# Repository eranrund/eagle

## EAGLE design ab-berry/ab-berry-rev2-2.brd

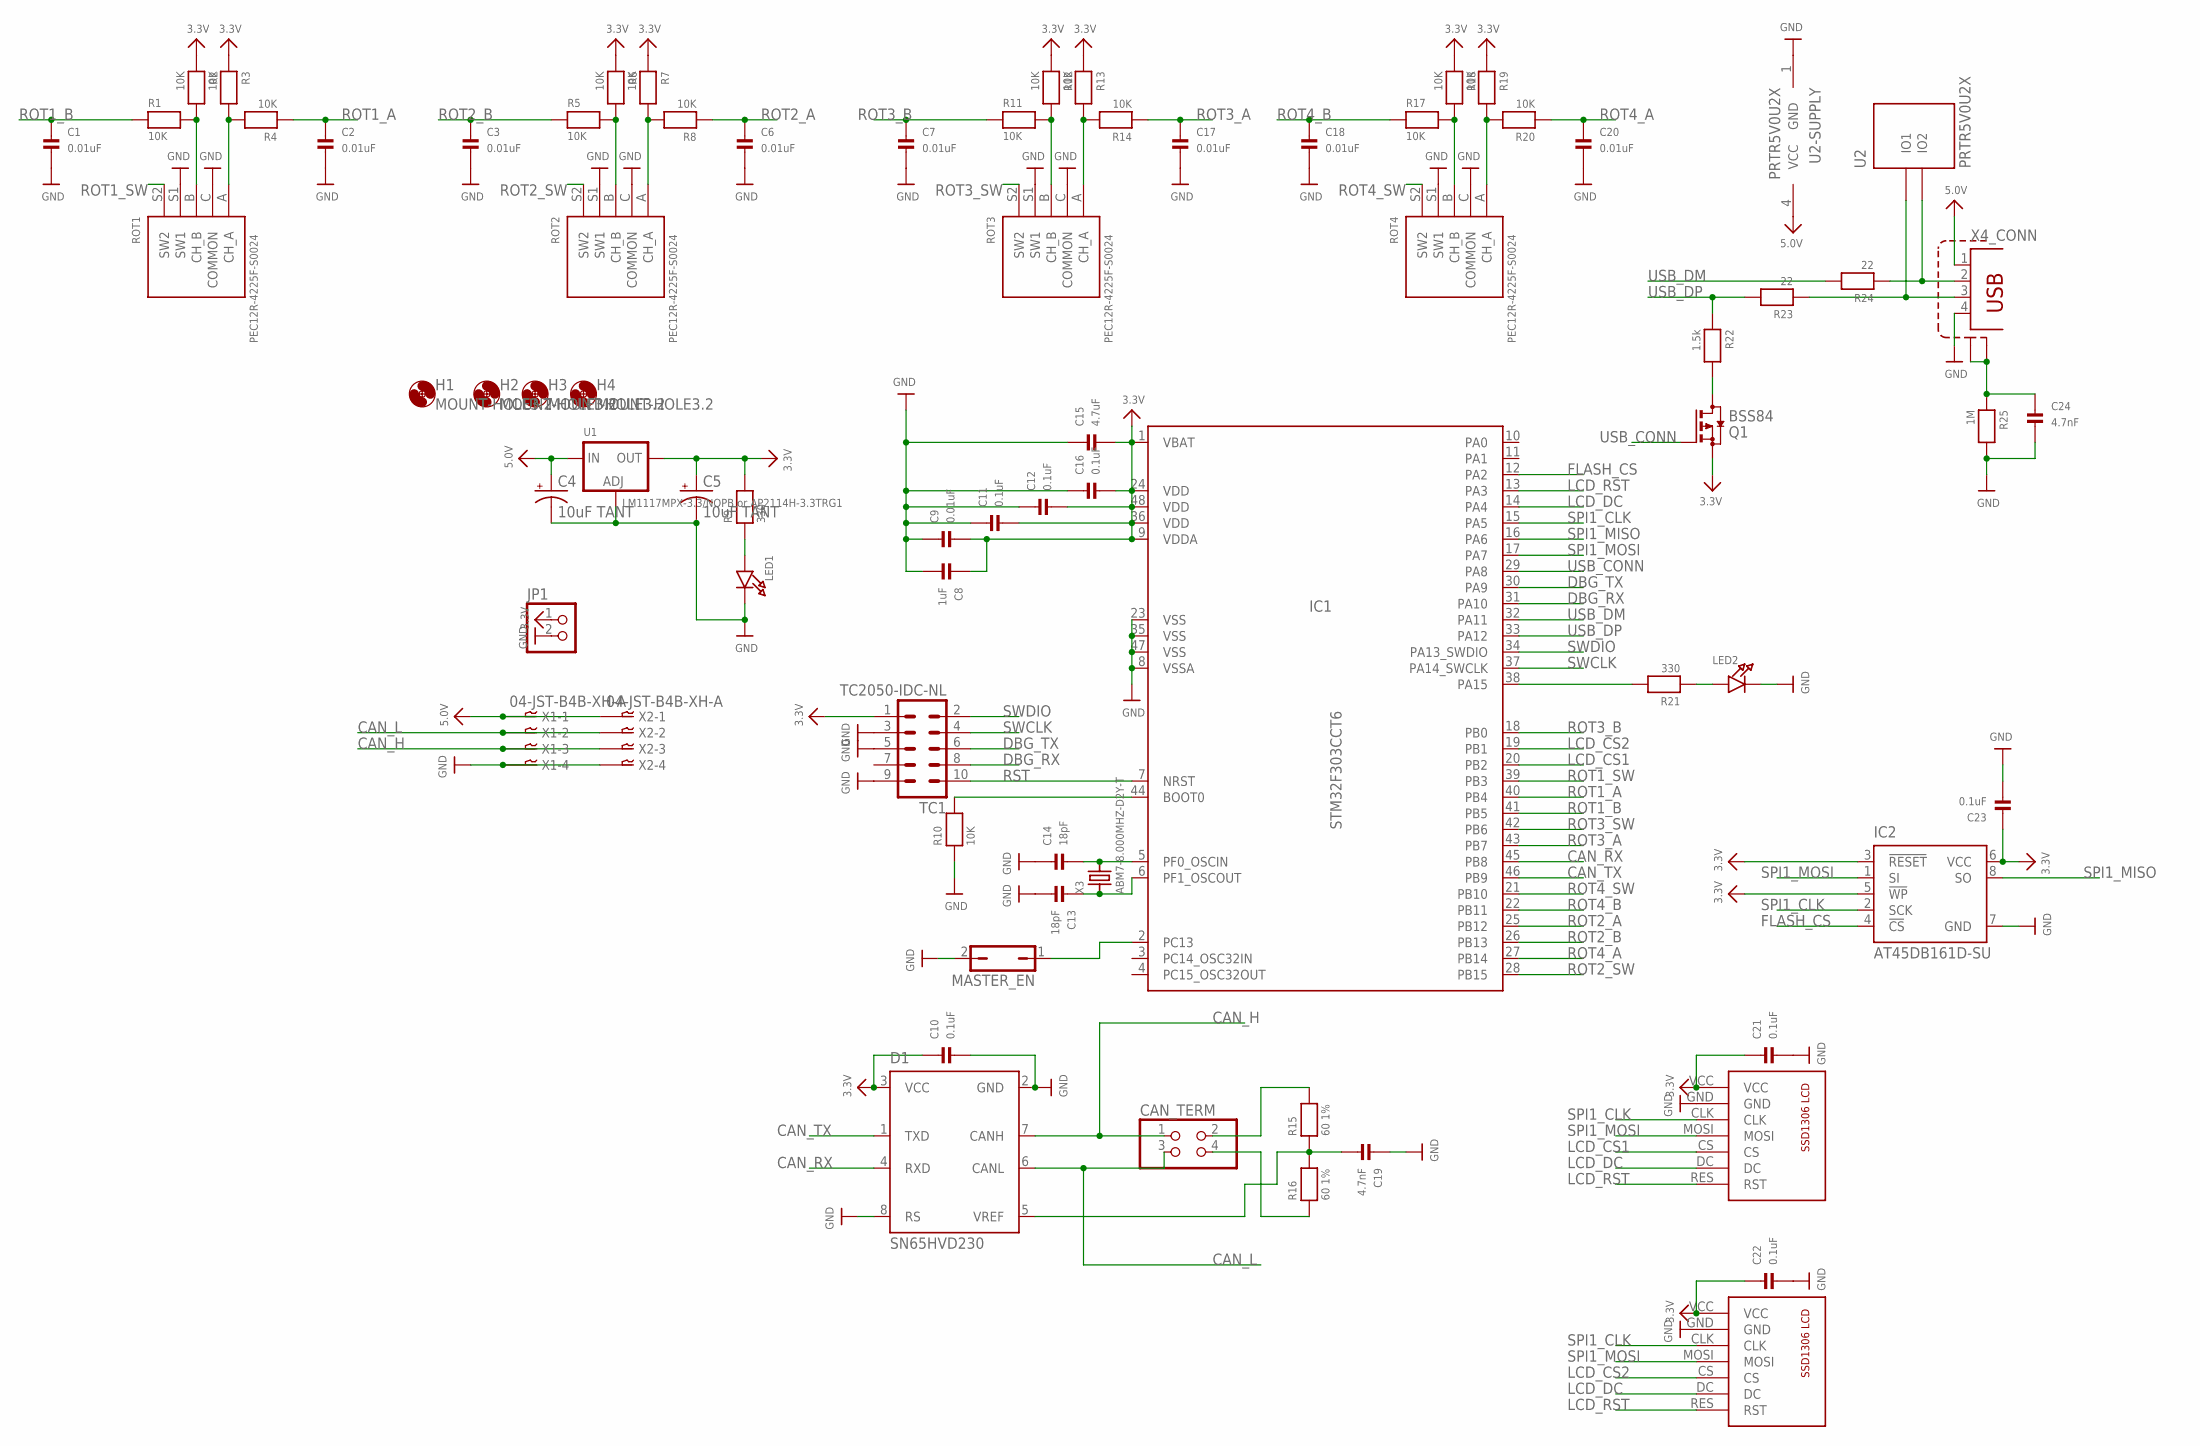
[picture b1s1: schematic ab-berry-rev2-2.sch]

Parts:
C1, C2, C3, C6, C7, C9, C17, C18, C20: 0.01uF; 0603
C4, C5: 10uF TANT; 0603-POL
C8: 1uF; 0603
C10, C11, C12, C16, C21, C22, C23: 0.1uF; 0603
C13, C14: 18pF; 0603
C15: 4.7uF; 0603
C19, C24: 4.7nF; 0603
CAN_TERM: PINHD-2X2; 2X02
D1: SN65HVD230; SO8
H1, H2, H3, H4: MOUNT-HOLE3.2; 3,2
IC1: STM32F303CCT6; TQFP48
IC2: AT45DB161D-SU; 8S2
JP1: PINHD-1X2; 1X02
LCD1, LCD2: SSD1306-7PINWITHOUT-HOLES; SSD1306-7PIN-NO-HOLES
LED1, LED2: LED0603; CHIPLED_0603
MASTER_EN: JP1Q; JP1
Q1: BSS84; SOT23
R1, R2, R3, R4, R5, R6, R7, R8, R10, R11, R12, R13, R14, R17, R18, R19, R20: 10K; 0603
R9, R21: 330; 0603
R15, R16: 60 1%; 0603
R22: 1.5k; 0603
R23, R24: 22; 0603
R25: 1M; 0603
ROT1, ROT2, ROT3, ROT4: PEC12R-4225F-S0024; PEC111-4XXXK-SXXXX
TC1: TC2050-IDC-NL
U1: LM1117MPX-3.3/NOPB or AP2114H-3.3TRG1; SOT223-R
U2: PRTR5V0U2X; SOT-143B
X1, X2: 04-JST-B4B-XH-A; B4B-XH
X3: ABM7-8.000MHZ-D2Y-T
X4: TE-292304-1

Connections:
3.3V: C5.A (+), C8.1, C9.2, C10.1, C11.2, C12.2, C15.2, C16.2, C21.1, C22.1, C23.1, D1.3 (VCC), IC1.1 (VBAT), IC1.9 (VDDA), IC1.24 (VDD), IC1.36 (VDD), IC1.48 (VDD), IC2.3 (!RESET), IC2.5 (!WP), IC2.6 (VCC), JP1.1, LCD1.VCC, LCD2.VCC, Q1.2 (S), R2.1, R3.1, R6.1, R7.1, R9.2, R12.1, R13.1, R18.1, R19.1, TC1.1, U1.2 (OUT)
5.0V: C4.A (+), U1.3 (IN), U2.4 (VCC), X1.P$1, X2.P$1, X4.1
CAN_H: CAN_TERM.1, D1.7 (CANH), X1.P$3, X2.P$3
CAN_L: CAN_TERM.3, D1.6 (CANL), X1.P$2, X2.P$2
CAN_RX: D1.4 (RXD), IC1.45 (PB8)
CAN_TX: D1.1 (TXD), IC1.46 (PB9)
DBG_RX: IC1.31 (PA10), TC1.8
DBG_TX: IC1.30 (PA9), TC1.6
FLASH_CS: IC1.12 (PA2), IC2.4 (!CS)
GND: C1.2, C2.2, C3.2, C4.K (-), C5.K (-), C6.2, C7.2, C8.2, C9.1, C10.2, C11.1, C12.1, C13.2, C14.1, C15.1, C16.1, C17.2, C18.2, C19.1, C20.2, C21.2, C22.2, C23.2, C24.2, D1.2 (GND), D1.8 (RS), IC1.8 (VSSA), IC1.23 (VSS), IC1.35 (VSS), IC1.47 (VSS), IC2.7 (GND), JP1.2, LCD1.GND, LCD2.GND, LED1.C, LED2.C, MASTER_EN.2, R10.1, R25.2, ROT1.C (COMMON), ROT1.S1 (SW1), ROT2.C (COMMON), ROT2.S1 (SW1), ROT3.C (COMMON), ROT3.S1 (SW1), ROT4.C (COMMON), ROT4.S1 (SW1), TC1.3, TC1.5, TC1.9, U1.1 (ADJ), U2.1 (GND), X1.P$4, X2.P$4, X4.4
LCD_CS1: IC1.20 (PB2), LCD1.CS
LCD_CS2: IC1.19 (PB1), LCD2.CS
LCD_DC: IC1.14 (PA4), LCD1.DC, LCD2.DC
LCD_RST: IC1.13 (PA3), LCD1.RES (RST), LCD2.RES (RST)
unnamed: IC1.44 (BOOT0), R10.2
unnamed: C19.2, D1.5 (VREF), R15.1, R16.2
unnamed: LED1.A, R9.1
unnamed: CAN_TERM.2, R15.2
unnamed: CAN_TERM.4, R16.1
unnamed: IC1.38 (PA15), R21.2
unnamed: LED2.A, R21.1
unnamed: C14.2, IC1.5 (PF0_OSCIN), X3.P$2 (2)
unnamed: C13.1, IC1.6 (PF1_OSCOUT), X3.P$1 (1)
unnamed: R5.2, R6.2, ROT2.B (CH_B)
unnamed: R7.2, R8.2, ROT2.A (CH_A)
unnamed: R17.2, R18.2, ROT4.B (CH_B)
unnamed: R19.2, R20.2, ROT4.A (CH_A)
unnamed: R1.2, R2.2, ROT1.B (CH_B)
unnamed: R3.2, R4.2, ROT1.A (CH_A)
unnamed: R11.2, R12.2, ROT3.B (CH_B)
unnamed: R13.2, R14.2, ROT3.A (CH_A)
unnamed: R24.1, U2.3 (IO2), X4.2
unnamed: R23.1, U2.2 (IO1), X4.3
unnamed: C24.1, R25.1, X4.P$1 (S1), X4.P$2 (S2)
unnamed: Q1.3 (D), R22.2
unnamed: IC1.2 (PC13), MASTER_EN.1
ROT1_A: C2.1, IC1.40 (PB4), R4.1
ROT1_B: C1.1, IC1.41 (PB5), R1.1
ROT1_SW: IC1.39 (PB3), ROT1.S2 (SW2)
ROT2_A: C6.1, IC1.25 (PB12), R8.1
ROT2_B: C3.1, IC1.26 (PB13), R5.1
ROT2_SW: IC1.28 (PB15), ROT2.S2 (SW2)
ROT3_A: C17.1, IC1.43 (PB7), R14.1
ROT3_B: C7.1, IC1.18 (PB0), R11.1
ROT3_SW: IC1.42 (PB6), ROT3.S2 (SW2)
ROT4_A: C20.1, IC1.27 (PB14), R20.1
ROT4_B: C18.1, IC1.22 (PB11), R17.1
ROT4_SW: IC1.21 (PB10), ROT4.S2 (SW2)
RST: IC1.7 (NRST), TC1.10
SPI1_CLK: IC1.15 (PA5), IC2.2 (SCK), LCD1.CLK, LCD2.CLK
SPI1_MISO: IC1.16 (PA6), IC2.8 (SO)
SPI1_MOSI: IC1.17 (PA7), IC2.1 (SI), LCD1.MOSI, LCD2.MOSI
SWCLK: IC1.37 (PA14_SWCLK), TC1.4
SWDIO: IC1.34 (PA13_SWDIO), TC1.2
USB_CONN: IC1.29 (PA8), Q1.1 (G)
USB_DM: IC1.32 (PA11), R24.2
USB_DP: IC1.33 (PA12), R22.1, R23.2

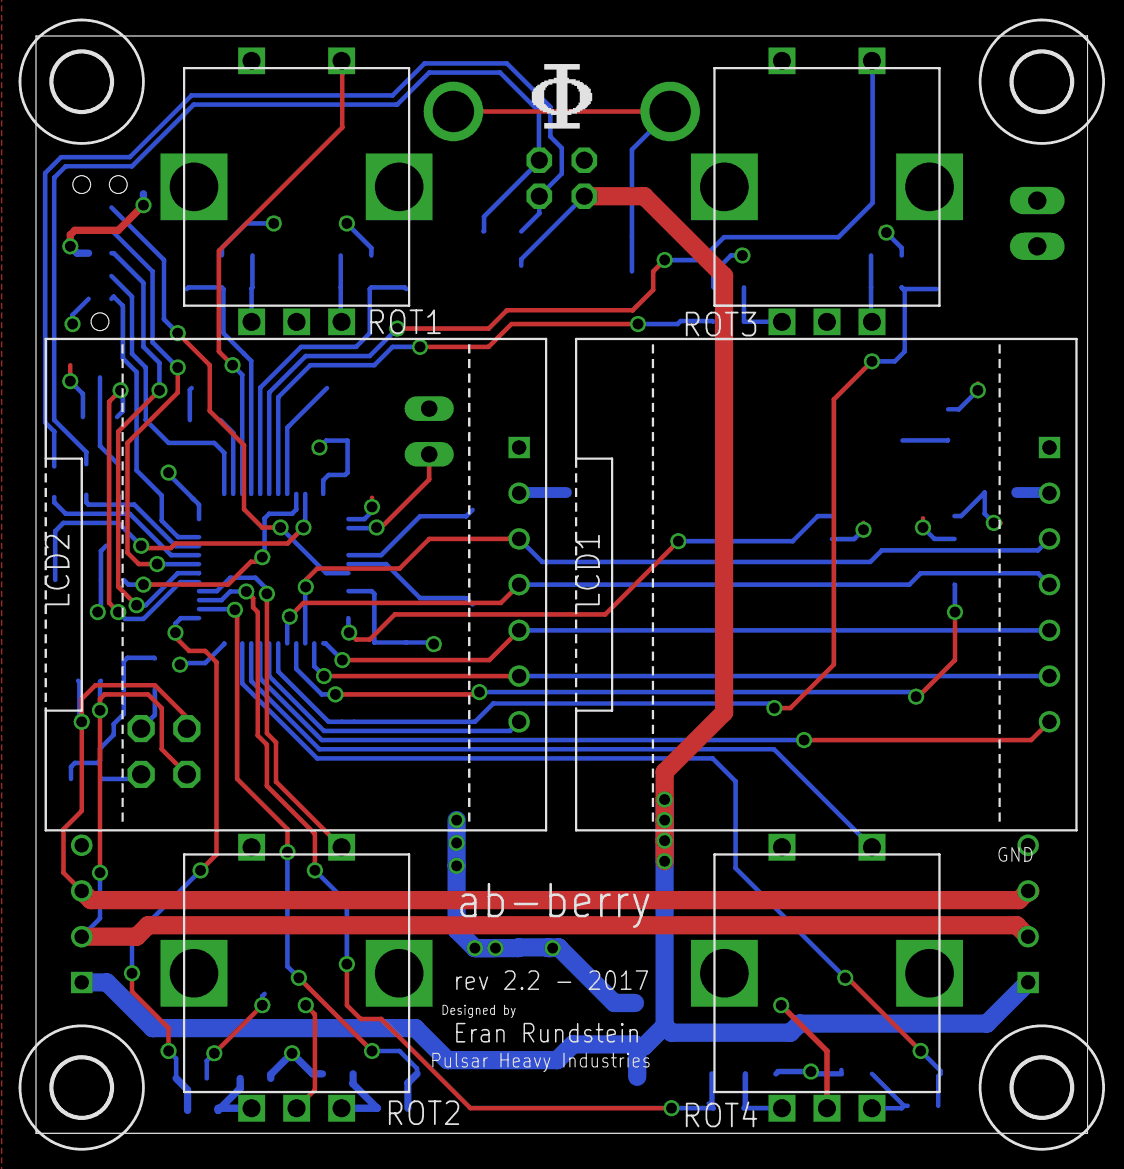
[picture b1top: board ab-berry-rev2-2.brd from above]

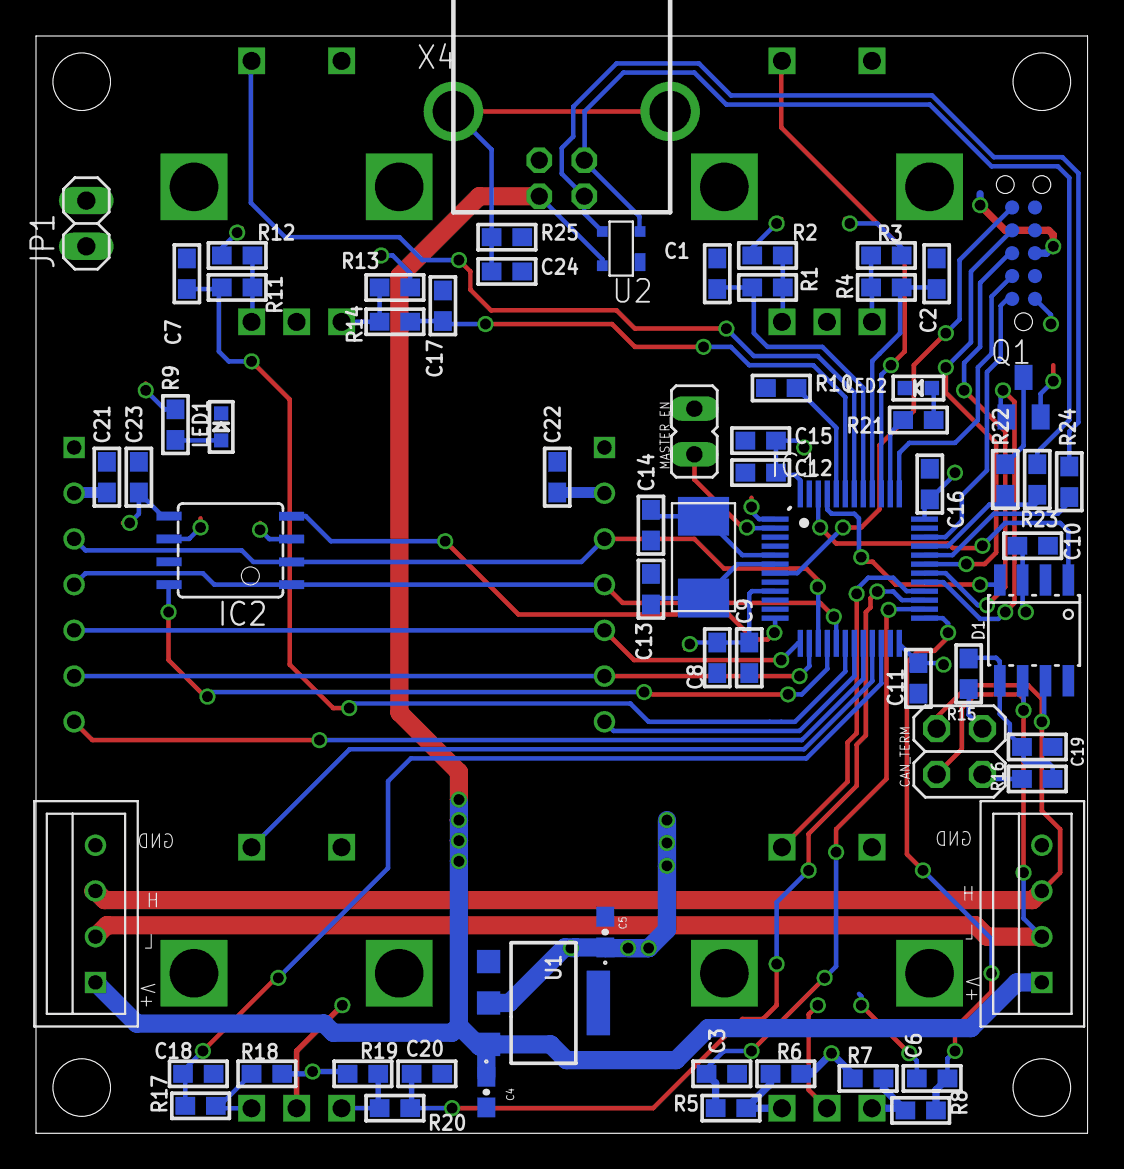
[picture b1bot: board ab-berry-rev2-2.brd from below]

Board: 2 copper layers, 58.4 x 61.0 mm, 75 parts (65 on the bottom side), 57 nets.

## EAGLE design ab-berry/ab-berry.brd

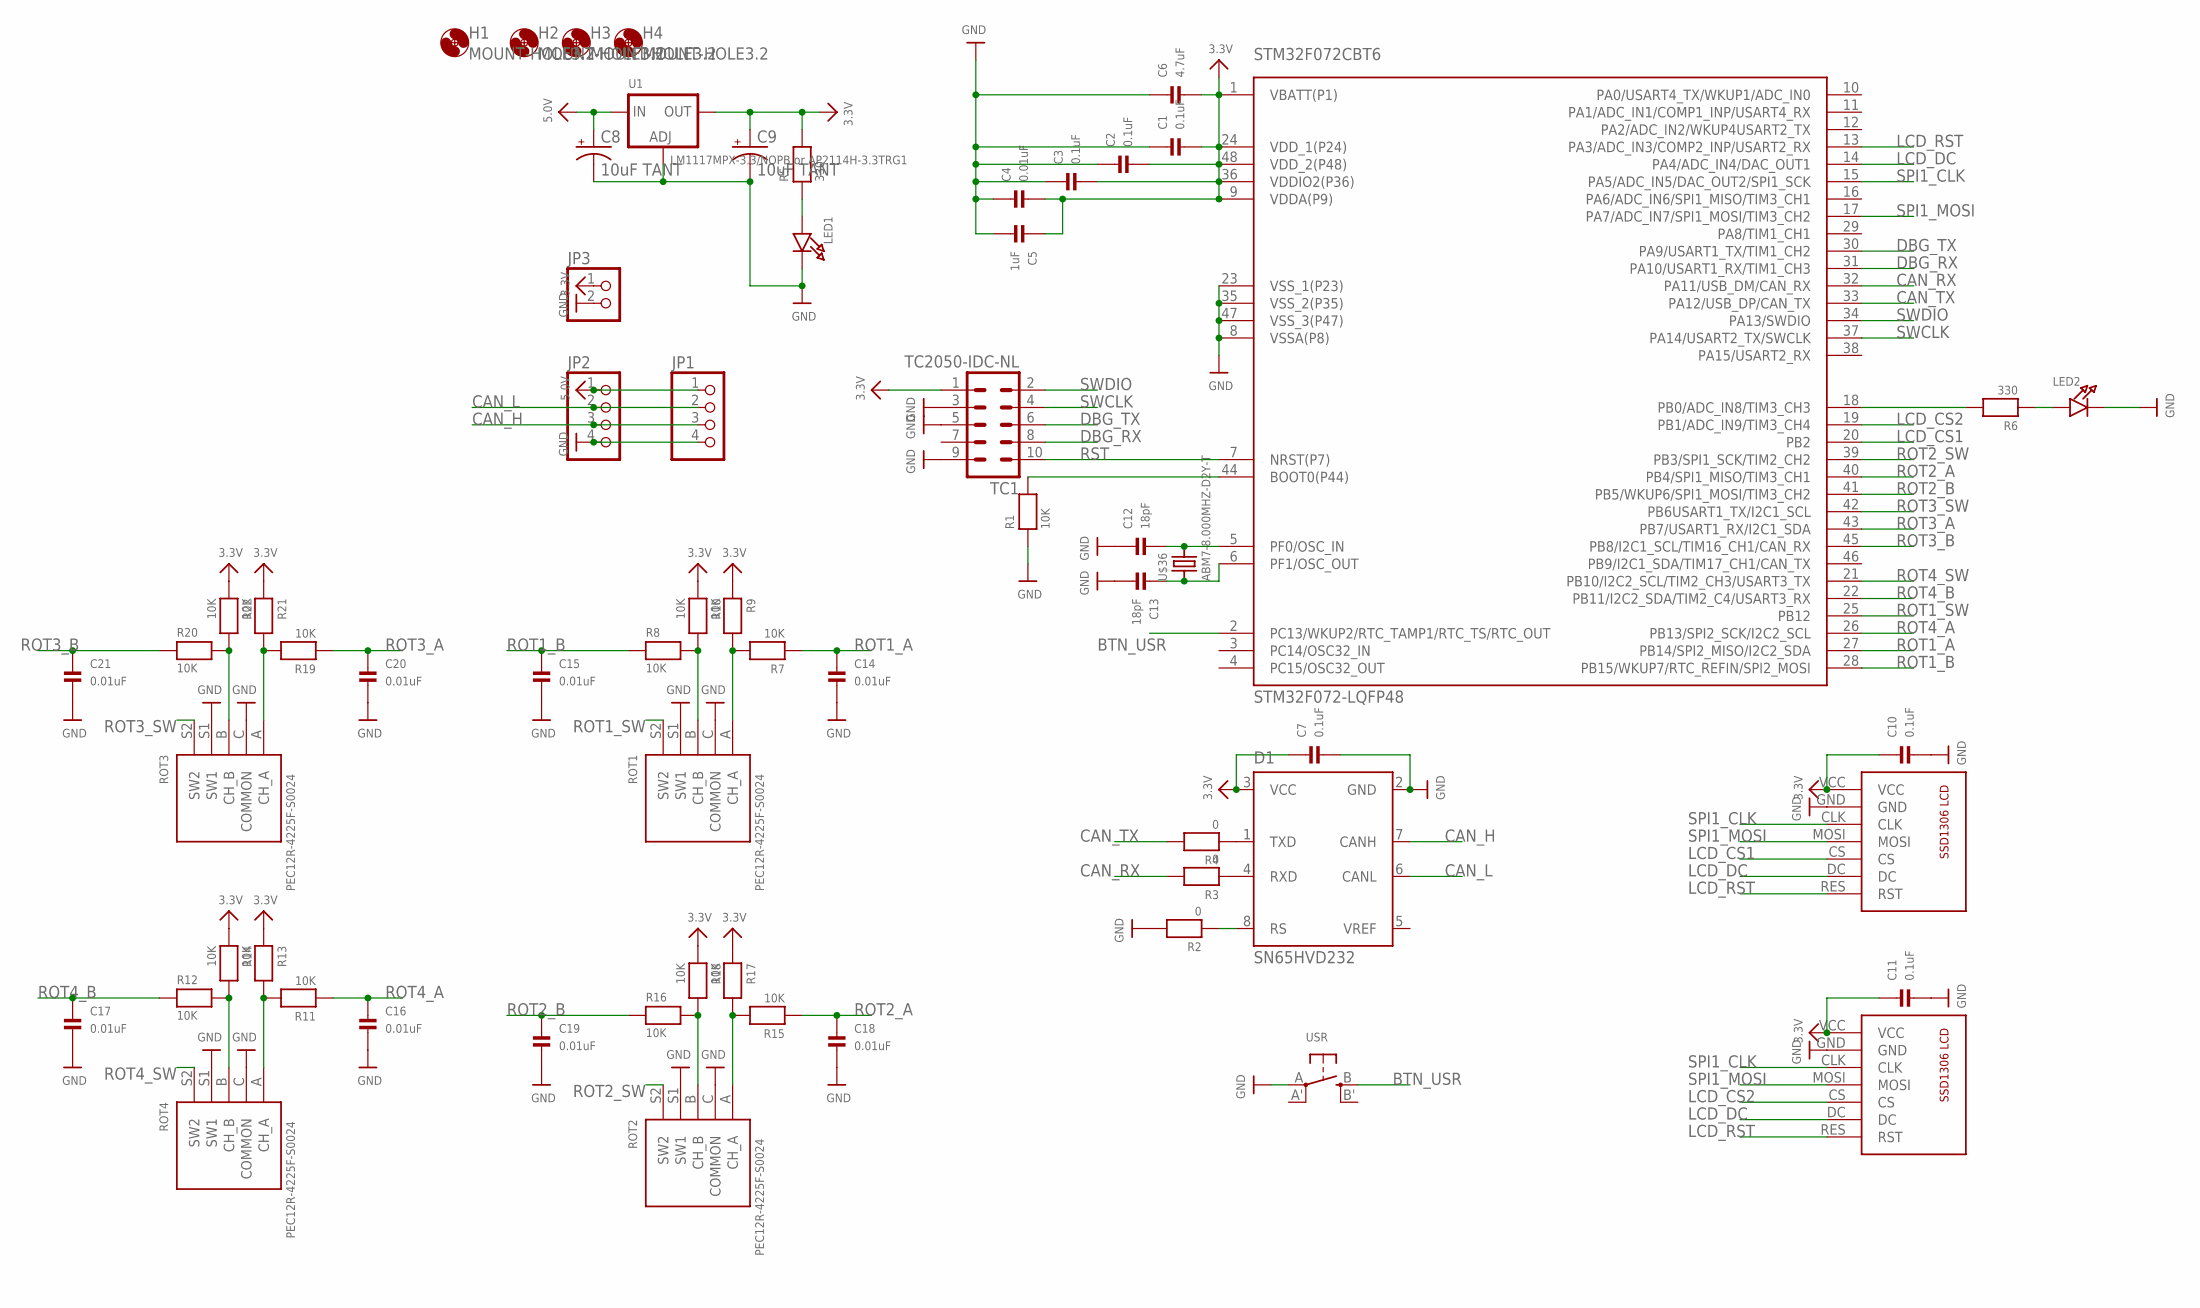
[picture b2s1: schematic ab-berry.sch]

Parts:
C1, C2, C3, C7, C10, C11: 0.1uF; 0603
C4, C14, C15, C16, C17, C18, C19, C20, C21: 0.01uF; 0603
C5: 1uF; 0603
C6: 4.7uF; 0603
C8, C9: 10uF TANT; 0603-POL
C12, C13: 18pF; 0603
D1: SN65HVD232; SO8
H1, H2, H3, H4: MOUNT-HOLE3.2; 3,2
JP1, JP2: PINHD-1X4; 1X04
JP3: PINHD-1X2; 1X02
LCD1, LCD2: SSD1306-7PIN
LED1, LED2: LED0603; CHIPLED_0603
R1, R7, R8, R9, R10, R11, R12, R13, R14, R15, R16, R17, R18, R19, R20, R21, R22: 10K; 0603
R2, R3, R4: 0; 0603
R5, R6: 330; 0603
ROT1, ROT2, ROT3, ROT4: PEC12R-4225F-S0024; PEC111-4XXXK-SXXXX
STM32F072CBT6: STM32F072-LQFP48; LQFP48
TC1: TC2050-IDC-NL
U1: LM1117MPX-3.3/NOPB or AP2114H-3.3TRG1; SOT223-R
U$36: ABM7-8.000MHZ-D2Y-T
USR: SWITCH_TACT_SMT; EVQ-Q2

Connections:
3.3V: C1.2, C2.2, C3.2, C4.2, C5.1, C6.2, C7.1, C9.A (+), C10.1, C11.1, D1.3 (VCC), JP3.1, LCD1.VCC, LCD2.VCC, R5.2, R9.1, R10.1, R13.1, R14.1, R17.1, R18.1, R21.1, R22.1, STM32F072CBT6.1 (VBATT(P1)), STM32F072CBT6.9 (VDDA(P9)), STM32F072CBT6.24 (VDD_1(P24)), STM32F072CBT6.36 (VDDIO2(P36)), STM32F072CBT6.48 (VDD_2(P48)), TC1.1, U1.2 (OUT)
5.0V: C8.A (+), JP1.1, JP2.1, U1.3 (IN)
BTN_USR: STM32F072CBT6.2 (PC13/WKUP2/RTC_TAMP1/RTC_TS/RTC_OUT), USR.B (S)
CAN_H: D1.7 (CANH), JP1.3, JP2.3
CAN_L: D1.6 (CANL), JP1.2, JP2.2
CAN_RX: R3.2, STM32F072CBT6.32 (PA11/USB_DM/CAN_RX)
CAN_TX: R4.2, STM32F072CBT6.33 (PA12/USB_DP/CAN_TX)
DBG_RX: STM32F072CBT6.31 (PA10/USART1_RX/TIM1_CH3), TC1.8
DBG_TX: STM32F072CBT6.30 (PA9/USART1_TX/TIM1_CH2), TC1.6
GND: C1.1, C2.1, C3.1, C4.1, C5.2, C6.1, C7.2, C8.K (-), C9.K (-), C10.2, C11.2, C12.1, C13.2, C14.2, C15.2, C16.2, C17.2, C18.2, C19.2, C20.2, C21.2, D1.2 (GND), JP1.4, JP2.4, JP3.2, LCD1.GND, LCD2.GND, LED1.C, LED2.C, R1.1, R2.2, ROT1.C (COMMON), ROT1.S1 (SW1), ROT2.C (COMMON), ROT2.S1 (SW1), ROT3.C (COMMON), ROT3.S1 (SW1), ROT4.C (COMMON), ROT4.S1 (SW1), STM32F072CBT6.8 (VSSA(P8)), STM32F072CBT6.23 (VSS_1(P23)), STM32F072CBT6.35 (VSS_2(P35)), STM32F072CBT6.47 (VSS_3(P47)), TC1.3, TC1.5, TC1.9, U1.1 (ADJ), USR.A
LCD_CS1: LCD1.CS, STM32F072CBT6.20 (PB2)
LCD_CS2: LCD2.CS, STM32F072CBT6.19 (PB1/ADC_IN9/TIM3_CH4)
LCD_DC: LCD1.DC, LCD2.DC, STM32F072CBT6.14 (PA4/ADC_IN4/DAC_OUT1)
LCD_RST: LCD1.RES (RST), LCD2.RES (RST), STM32F072CBT6.13 (PA3/ADC_IN3/COMP2_INP/USART2_RX)
unnamed: R1.2, STM32F072CBT6.44 (BOOT0(P44))
unnamed: D1.8 (RS), R2.1
unnamed: LED1.A, R5.1
unnamed: D1.4 (RXD), R3.1
unnamed: D1.1 (TXD), R4.1
unnamed: R6.2, STM32F072CBT6.18 (PB0/ADC_IN8/TIM3_CH3)
unnamed: LED2.A, R6.1
unnamed: C12.2, STM32F072CBT6.5 (PF0/OSC_IN), U$36.P$2 (2)
unnamed: C13.1, STM32F072CBT6.6 (PF1/OSC_OUT), U$36.P$1 (1)
unnamed: R8.2, R10.2, ROT1.B (CH_B)
unnamed: R7.2, R9.2, ROT1.A (CH_A)
unnamed: R12.2, R14.2, ROT4.B (CH_B)
unnamed: R11.2, R13.2, ROT4.A (CH_A)
unnamed: R16.2, R18.2, ROT2.B (CH_B)
unnamed: R15.2, R17.2, ROT2.A (CH_A)
unnamed: R20.2, R22.2, ROT3.B (CH_B)
unnamed: R19.2, R21.2, ROT3.A (CH_A)
ROT1_A: C14.1, R7.1, STM32F072CBT6.27 (PB14/SPI2_MISO/I2C2_SDA)
ROT1_B: C15.1, R8.1, STM32F072CBT6.28 (PB15/WKUP7/RTC_REFIN/SPI2_MOSI)
ROT1_SW: ROT1.S2 (SW2), STM32F072CBT6.25 (PB12)
ROT2_A: C18.1, R15.1, STM32F072CBT6.40 (PB4/SPI1_MISO/TIM3_CH1)
ROT2_B: C19.1, R16.1, STM32F072CBT6.41 (PB5/WKUP6/SPI1_MOSI/TIM3_CH2)
ROT2_SW: ROT2.S2 (SW2), STM32F072CBT6.39 (PB3/SPI1_SCK/TIM2_CH2)
ROT3_A: C20.1, R19.1, STM32F072CBT6.43 (PB7/USART1_RX/I2C1_SDA)
ROT3_B: C21.1, R20.1, STM32F072CBT6.45 (PB8/I2C1_SCL/TIM16_CH1/CAN_RX)
ROT3_SW: ROT3.S2 (SW2), STM32F072CBT6.42 (PB6USART1_TX/I2C1_SCL)
ROT4_A: C16.1, R11.1, STM32F072CBT6.26 (PB13/SPI2_SCK/I2C2_SCL)
ROT4_B: C17.1, R12.1, STM32F072CBT6.22 (PB11/I2C2_SDA/TIM2_C4/USART3_RX)
ROT4_SW: ROT4.S2 (SW2), STM32F072CBT6.21 (PB10/I2C2_SCL/TIM2_CH3/USART3_TX)
RST: STM32F072CBT6.7 (NRST(P7)), TC1.10
SPI1_CLK: LCD1.CLK, LCD2.CLK, STM32F072CBT6.15 (PA5/ADC_IN5/DAC_OUT2/SPI1_SCK)
SPI1_MOSI: LCD1.MOSI, LCD2.MOSI, STM32F072CBT6.17 (PA7/ADC_IN7/SPI1_MOSI/TIM3_CH2)
SWCLK: STM32F072CBT6.37 (PA14/USART2_TX/SWCLK), TC1.4
SWDIO: STM32F072CBT6.34 (PA13/SWDIO), TC1.2

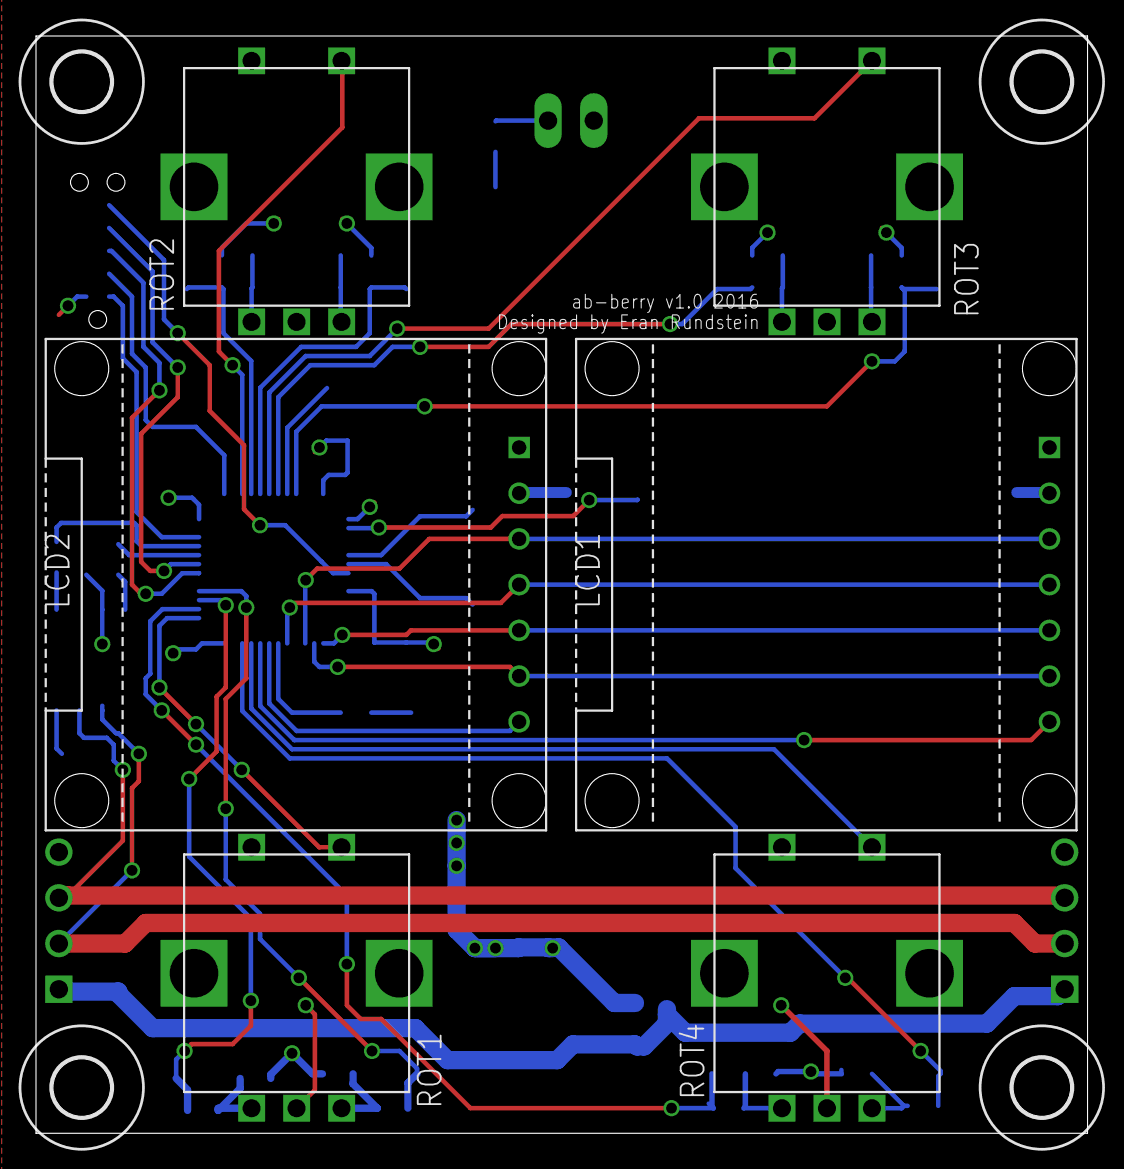
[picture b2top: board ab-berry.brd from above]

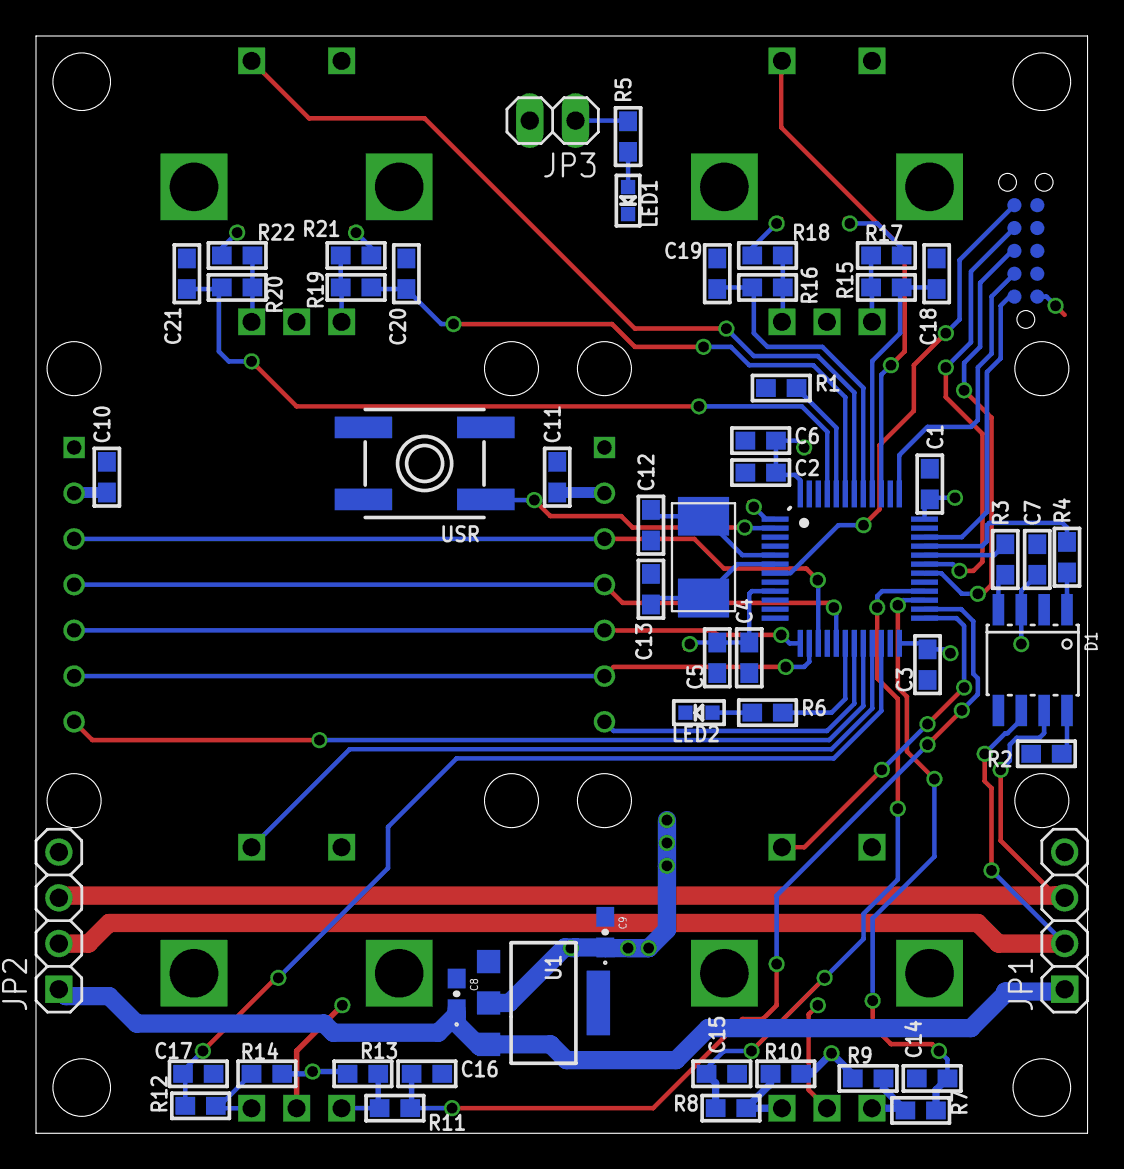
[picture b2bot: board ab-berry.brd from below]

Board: 2 copper layers, 58.4 x 61.0 mm, 64 parts (54 on the bottom side), 48 nets.

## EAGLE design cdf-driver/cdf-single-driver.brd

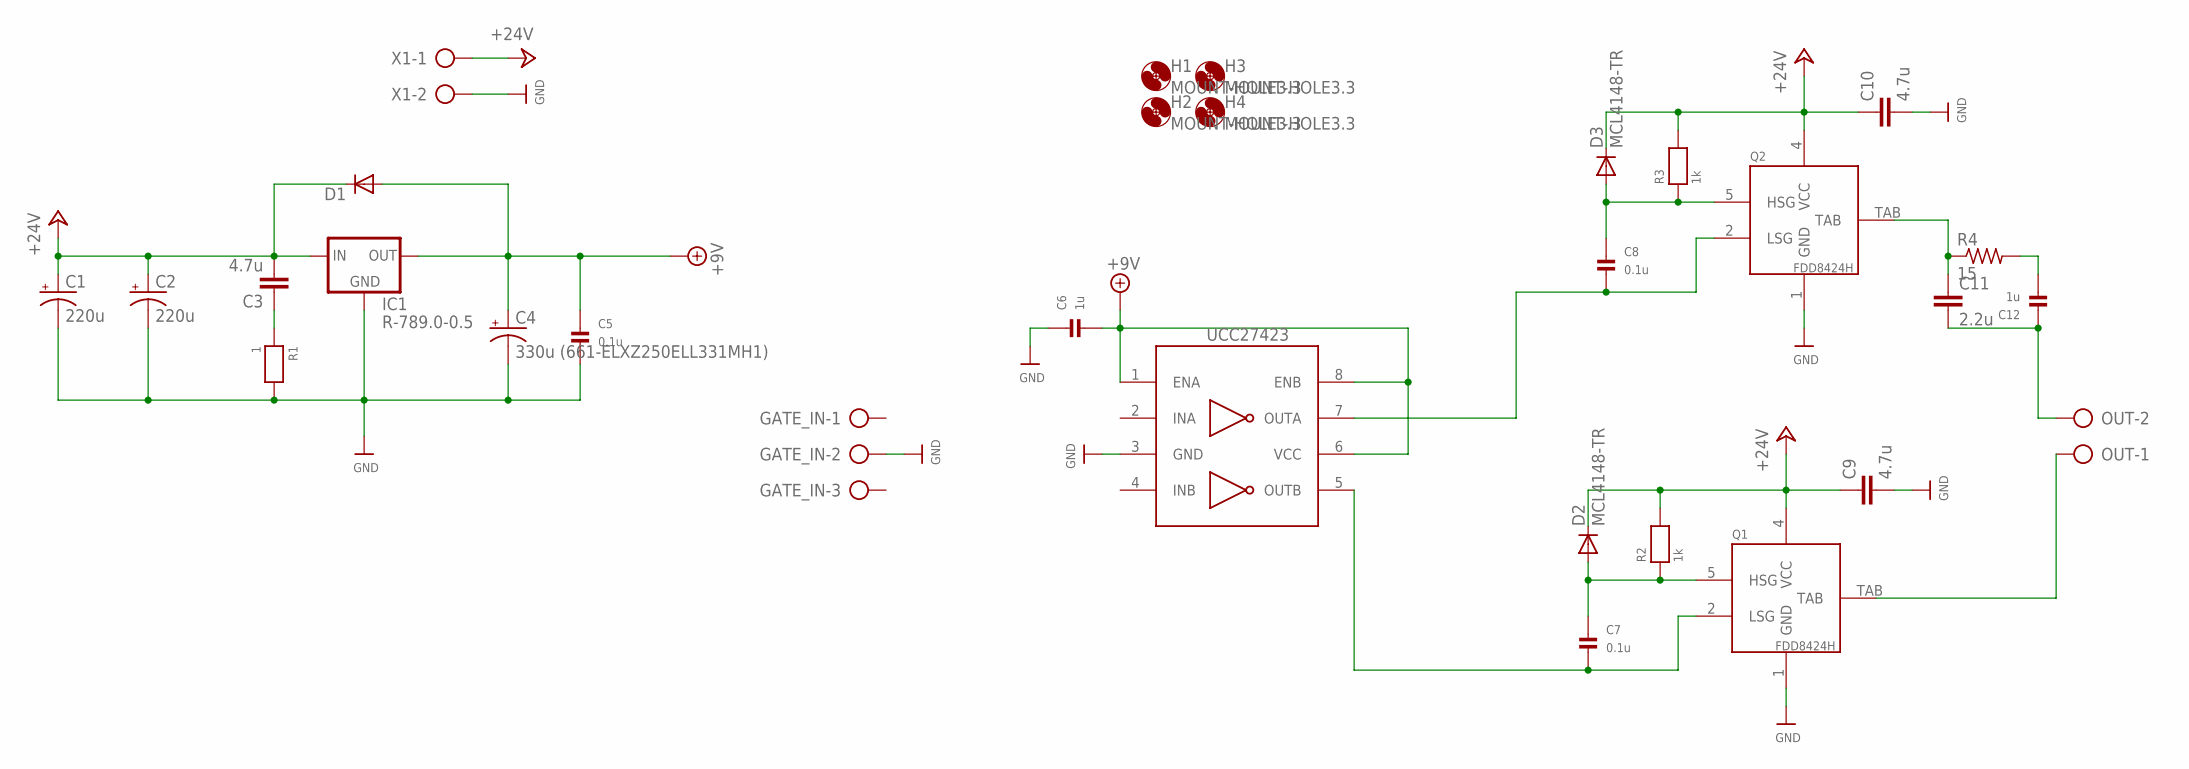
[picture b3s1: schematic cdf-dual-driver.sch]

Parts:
C1, C2: 220u; E3,5-8
C3, C9, C10: 4.7u; C1210
C4: 330u (661-ELXZ250ELL331MH1); E3,5-8
C5, C7, C8: 0.1u; 0805
C6, C12: 1u; 1206
C11: 2.2u; C1210
D1: DIODE-SOD123; SOD123
D2, D3: MCL4148-TR; MICROMELF-W
GATE_IN: AK500/3
H1, H2, H3, H4: MOUNT-HOLE3.3; 3,3
IC1: R-789.0-0.5; SIP3
IC2: UCC27423; SOIC8
OUT: AK500/2
Q1, Q2: FDD8424H; TO252-4
R1: 1; 0805
R2, R3: 1k; 0805
R4: 15; R1210
X1: AK500/2

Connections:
+9V: C4.+, C5.1, C6.2, D1.A, IC1.3 (OUT), IC2.1 (ENA), IC2.6 (VCC), IC2.8 (ENB)
+24V: C1.+, C2.+, C3.2, C9.1, C10.1, D1.C, D2.C, D3.C, IC1.1 (IN), Q1.4 (VCC), Q2.4 (VCC), R2.2, R3.2, X1.1
GND: C1.-, C2.-, C4.-, C5.2, C6.1, C9.2, C10.2, GATE_IN.2, IC1.2 (GND), IC2.3 (GND), Q1.1 (GND), Q2.1 (GND), R1.2, X1.2
unnamed: GATE_IN.1, IC2.2 (INA)
unnamed: GATE_IN.3, IC2.4 (INB)
unnamed: C8.2, IC2.7 (OUTA), Q2.2 (LSG)
unnamed: C8.1, D3.A, Q2.5 (HSG), R3.1
unnamed: C11.1, Q2.TAB, R4.1
unnamed: C12.2, R4.2
unnamed: C11.2, C12.1, OUT.2
unnamed: C7.2, IC2.5 (OUTB), Q1.2 (LSG)
unnamed: C7.1, D2.A, Q1.5 (HSG), R2.1
unnamed: OUT.1, Q1.TAB
unnamed: C3.1, R1.1

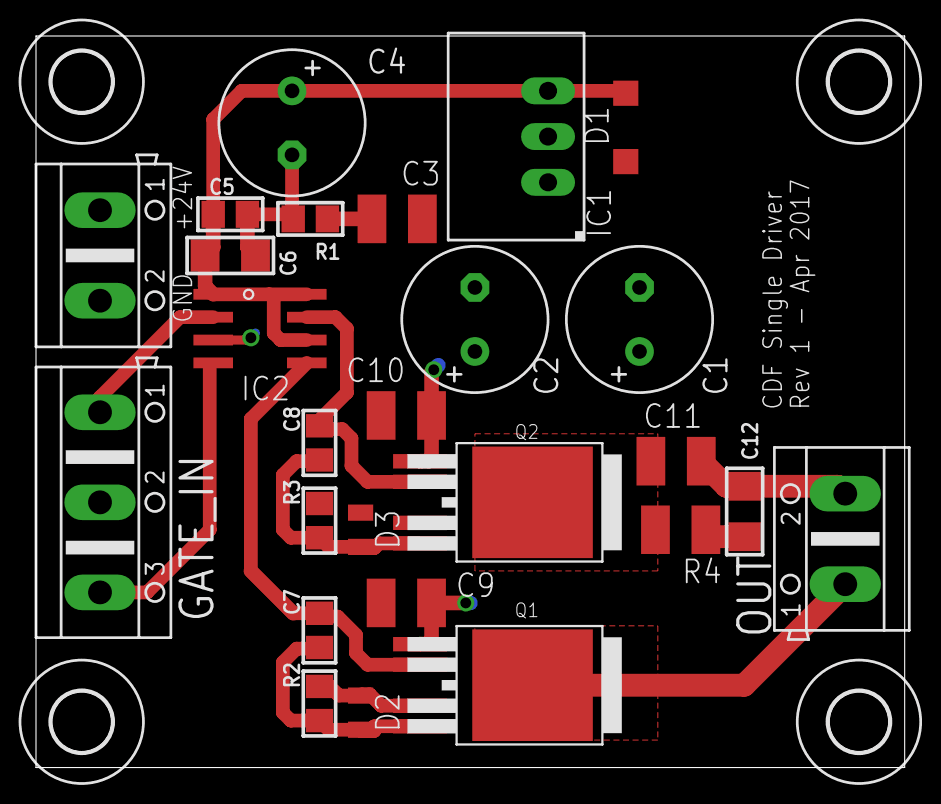
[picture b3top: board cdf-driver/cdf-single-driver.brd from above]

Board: 2 copper layers, 48.3 x 40.6 mm, 30 parts (0 on the bottom side), 14 nets.

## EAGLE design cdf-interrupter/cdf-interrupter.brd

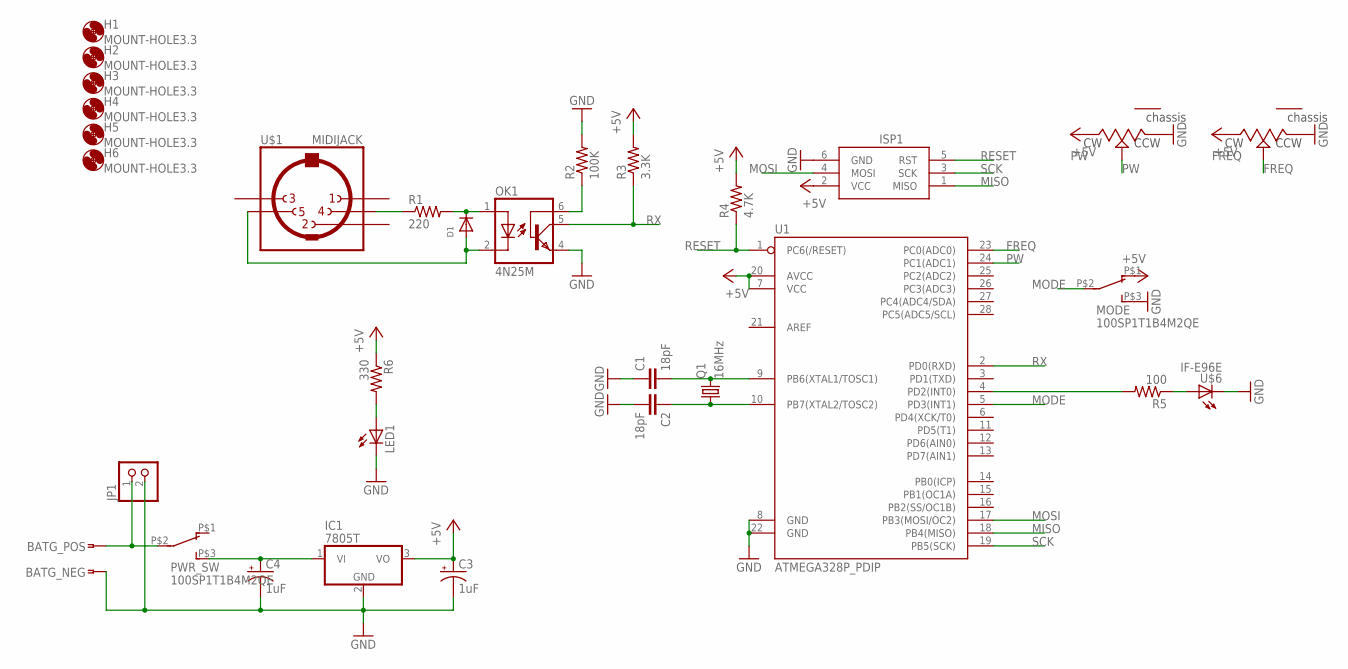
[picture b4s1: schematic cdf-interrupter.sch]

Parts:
BAT: KEYSTONE-9V-BAT-HOLDER-1291
C1, C2: 18pF; C050-025X075
C3, C4: 1uF; E2-4
D1: DIODEDO-1N4148; DO-1N4148
FREQ: POTENTIOMETERPTV09A_VERTICAL; PTV09A-4
H1, H2, H3, H4, H5, H6: MOUNT-HOLE3.3; 3,3
IC1: 7805T; TO220H
ISP1: AVRISP-BOX
JP1: PINHD-1X2; 1X02
LED1: LED5MM
MODE: 100SP1T1B4M2QE
OK1: 4N25M; DIL06
PW: POTENTIOMETERPTV09A_VERTICAL; PTV09A-4
PWR_SW: 100SP1T1B4M2QE
Q1: 16MHz; HC49UP
R1: 220; 0204/7
R2: 100K; 0204/7
R3: 3.3K; 0204/7
R4: 4.7K; 0204/7
R5: 100; 0204/7
R6: 330; 0204/7
U1: ATMEGA328P_PDIP; DIL28-3
U$1: MIDIJACK; CP-2350
U$6: IF-E96E

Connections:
+5V: C3.+, FREQ.3 (CW), IC1.3 (VO), ISP1.2 (VCC), MODE.P$1 (1), PW.3 (CW), R3.2, R4.2, R6.1, U1.7 (VCC), U1.20 (AVCC)
FREQ: FREQ.2 (WIPER), U1.23 (PC0(ADC0))
GND: BAT.P_NEG, C1.1, C2.2, C3.-, C4.-, FREQ.1 (CCW), IC1.2 (GND), ISP1.6 (GND), JP1.2, LED1.K (C), MODE.P$3 (3), OK1.4 (EMI), PW.1 (CCW), R2.2, U1.8 (GND), U1.22 (GND), U$6.P$1_CATHODE- (C)
MISO: ISP1.1 (MISO), U1.18 (PB4(MISO))
MODE: MODE.P$2 (2), U1.5 (PD3(INT1))
MOSI: ISP1.4 (MOSI), U1.17 (PB3(MOSI/OC2))
unnamed: R1.1, U$1.4
unnamed: D1.C, OK1.1 (A), R1.2
unnamed: D1.A, OK1.2 (C), U$1.5
unnamed: OK1.6 (BAS), R2.1
unnamed: C1.2, Q1.2, U1.9 (PB6(XTAL1/TOSC1))
unnamed: C2.1, Q1.1, U1.10 (PB7(XTAL2/TOSC2))
unnamed: R5.2, U1.4 (PD2(INT0))
unnamed: R5.1, U$6.P$2_ANODE+ (A)
unnamed: LED1.A, R6.2
unnamed: BAT.P_POS, JP1.1, PWR_SW.P$2 (2)
unnamed: C4.+, IC1.1 (VI), PWR_SW.P$3 (3)
PW: PW.2 (WIPER), U1.24 (PC1(ADC1))
RESET: ISP1.5 (RST), R4.1, U1.1 (PC6(/RESET))
RX: OK1.5 (COL), R3.1, U1.2 (PD0(RXD))
SCK: ISP1.3 (SCK), U1.19 (PB5(SCK))

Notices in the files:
parts and their libraries:
microbuilder: This work is placed in the public domain, and may be freely used for commercial and non-commercial work with the following conditions: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
SparkFun-Capacitors: Licensing: Creative Commons ShareAlike 4.0 International - https://creativecommons.org/licenses/by-sa/4.0
